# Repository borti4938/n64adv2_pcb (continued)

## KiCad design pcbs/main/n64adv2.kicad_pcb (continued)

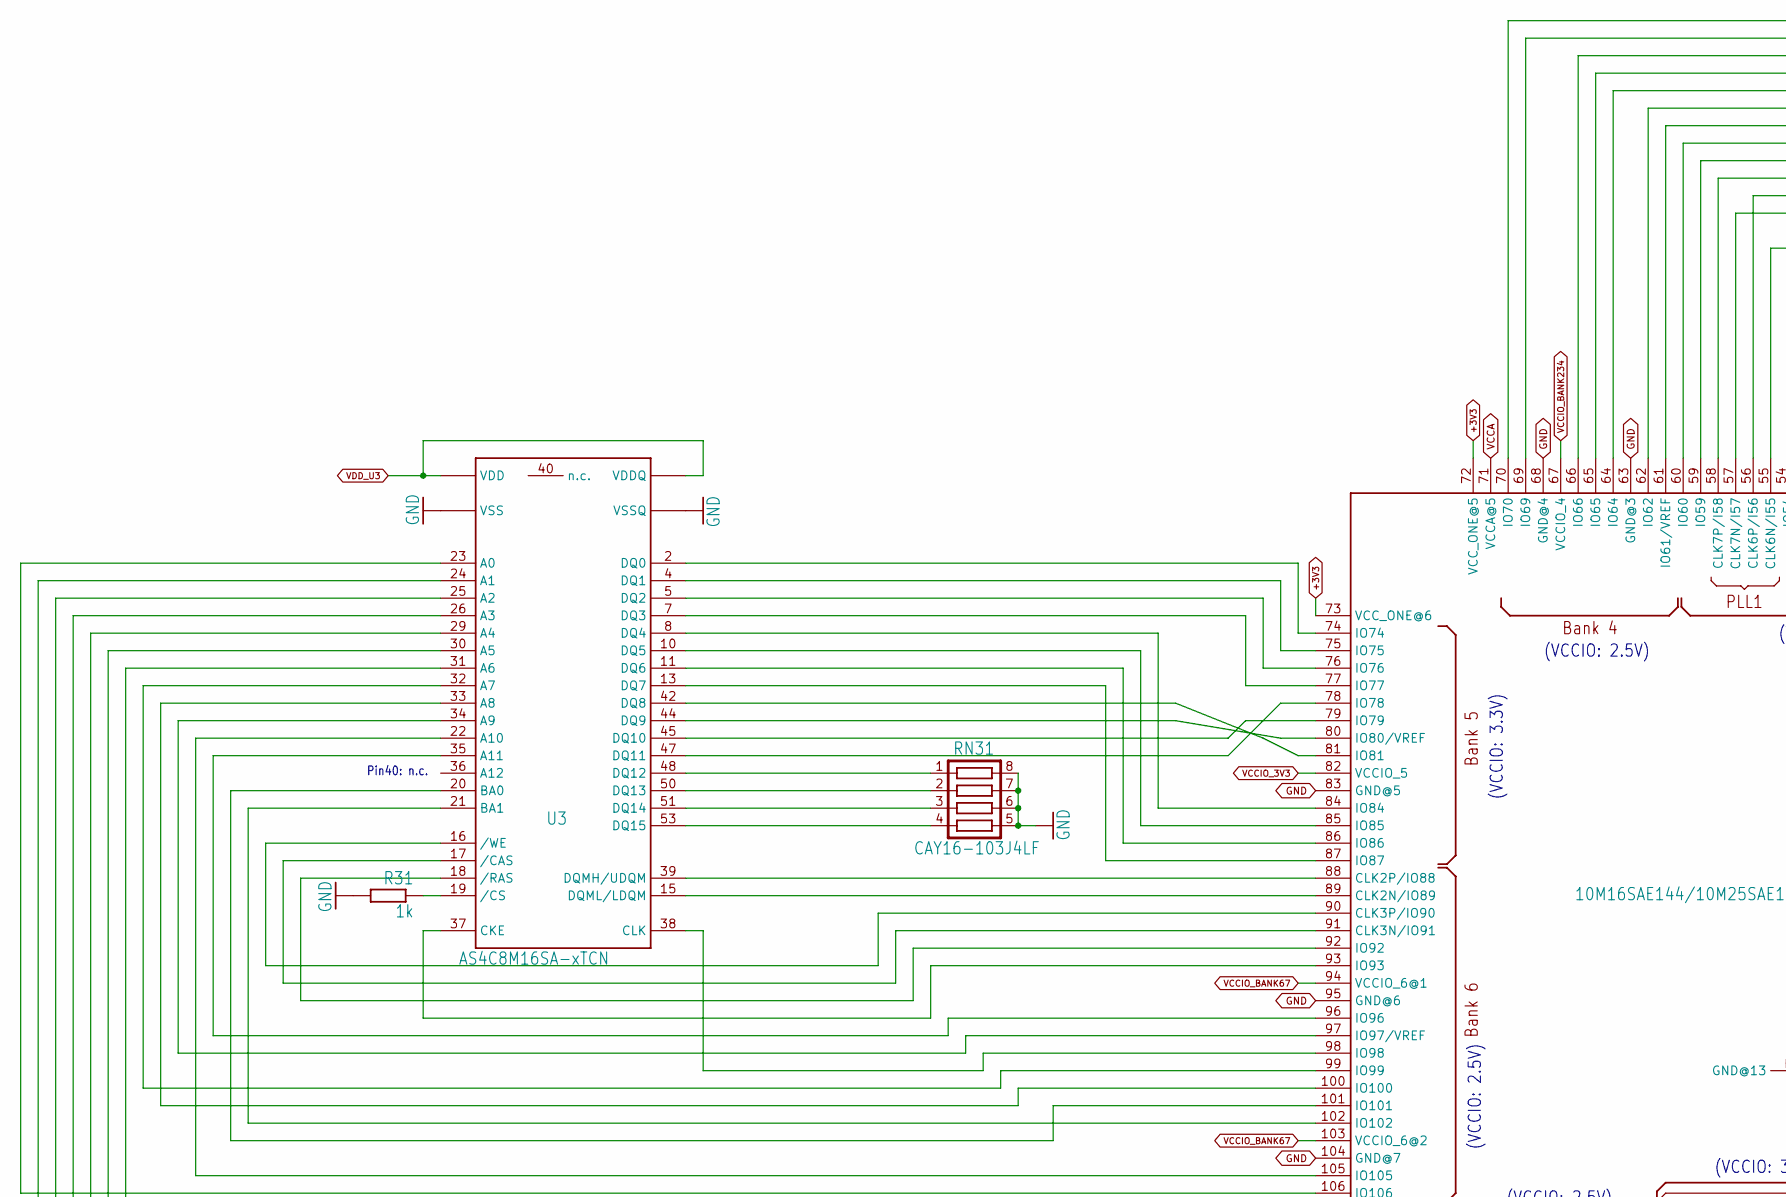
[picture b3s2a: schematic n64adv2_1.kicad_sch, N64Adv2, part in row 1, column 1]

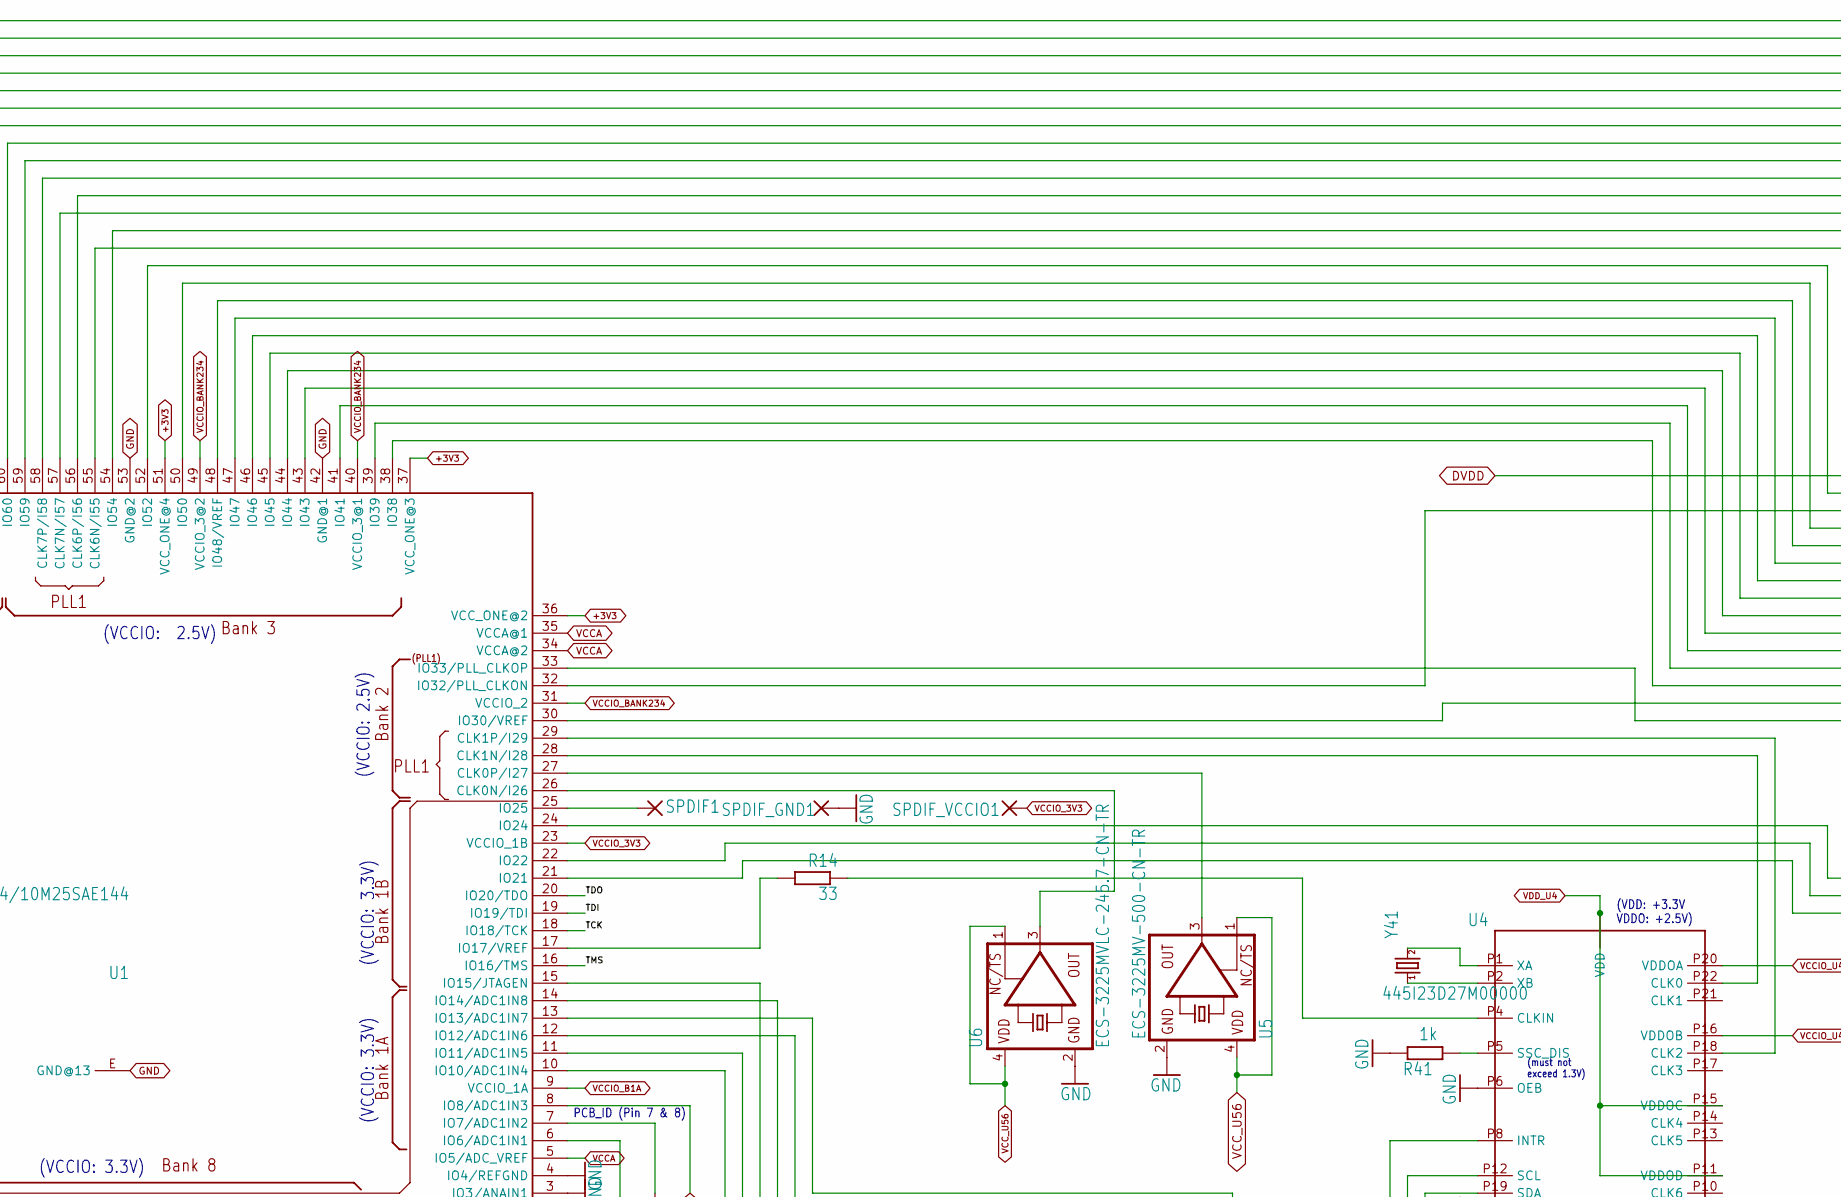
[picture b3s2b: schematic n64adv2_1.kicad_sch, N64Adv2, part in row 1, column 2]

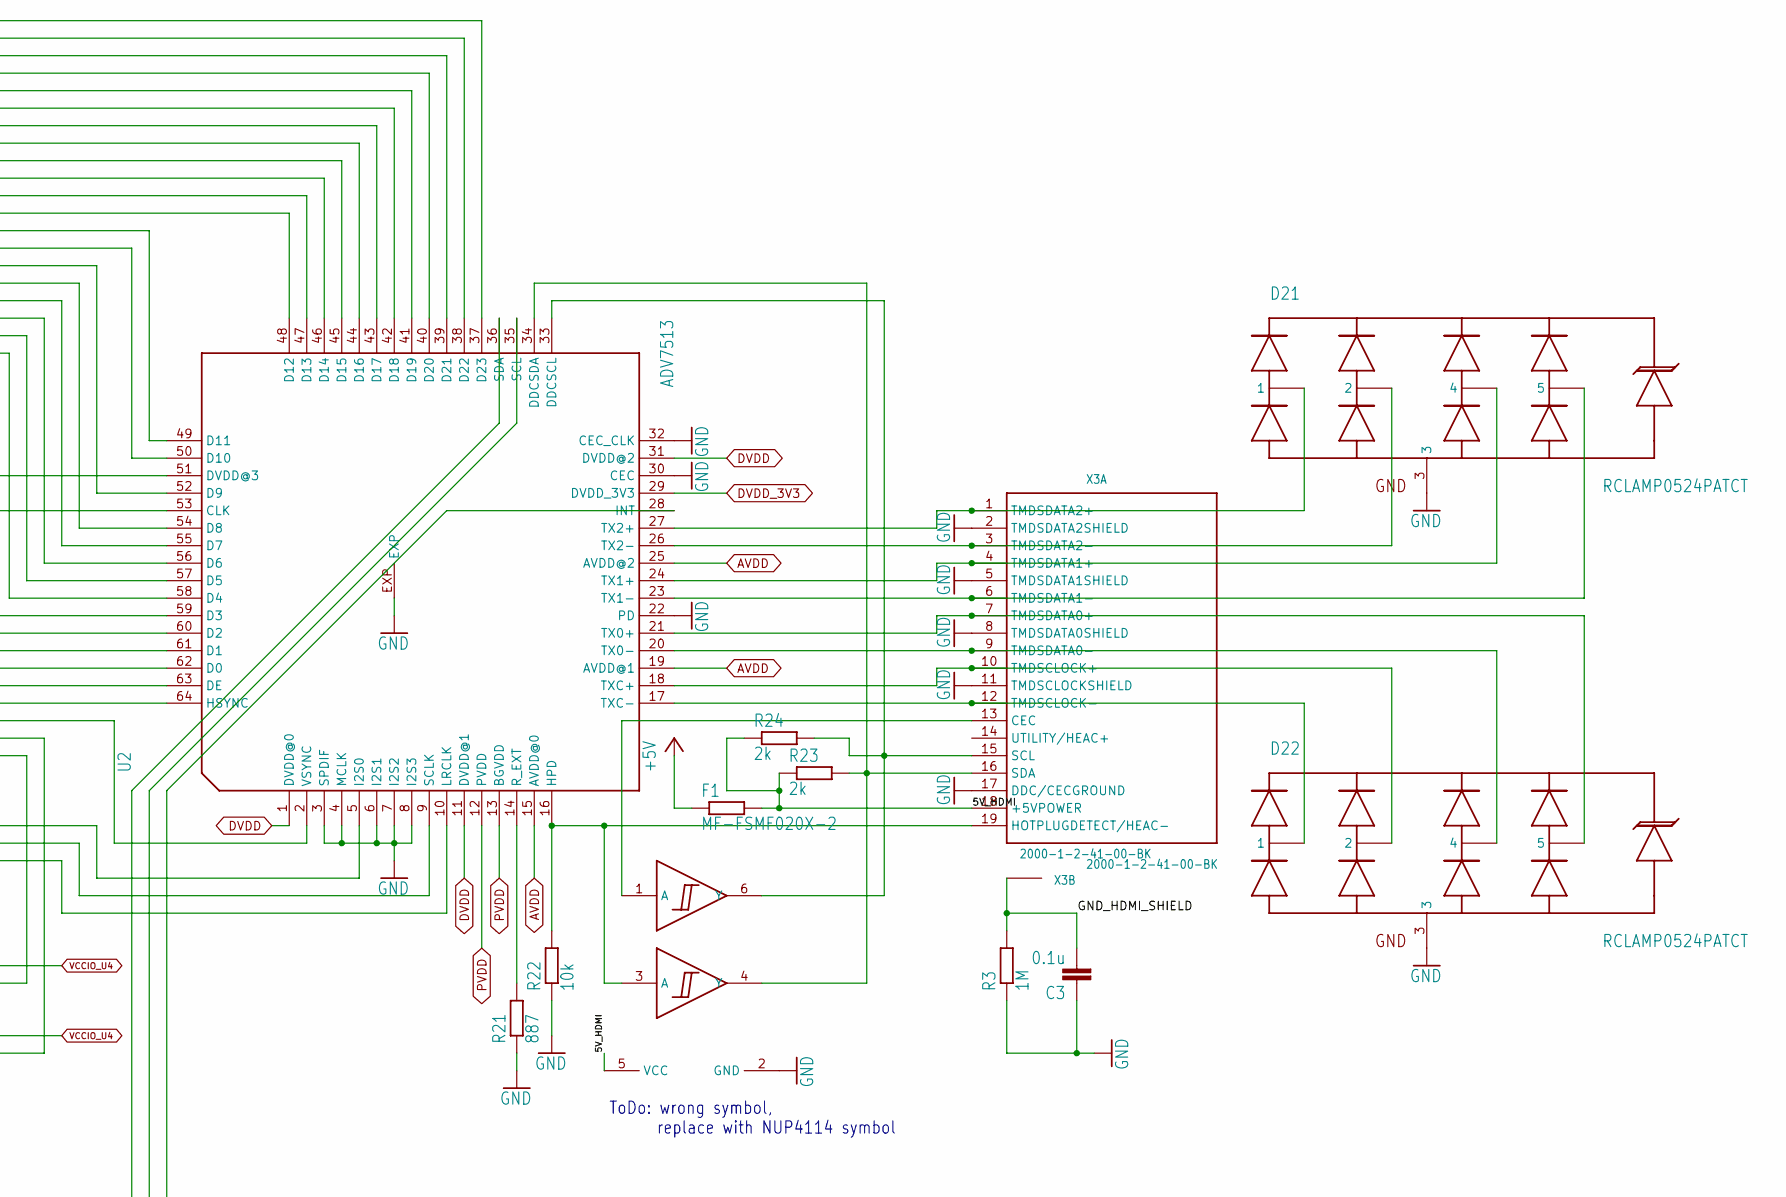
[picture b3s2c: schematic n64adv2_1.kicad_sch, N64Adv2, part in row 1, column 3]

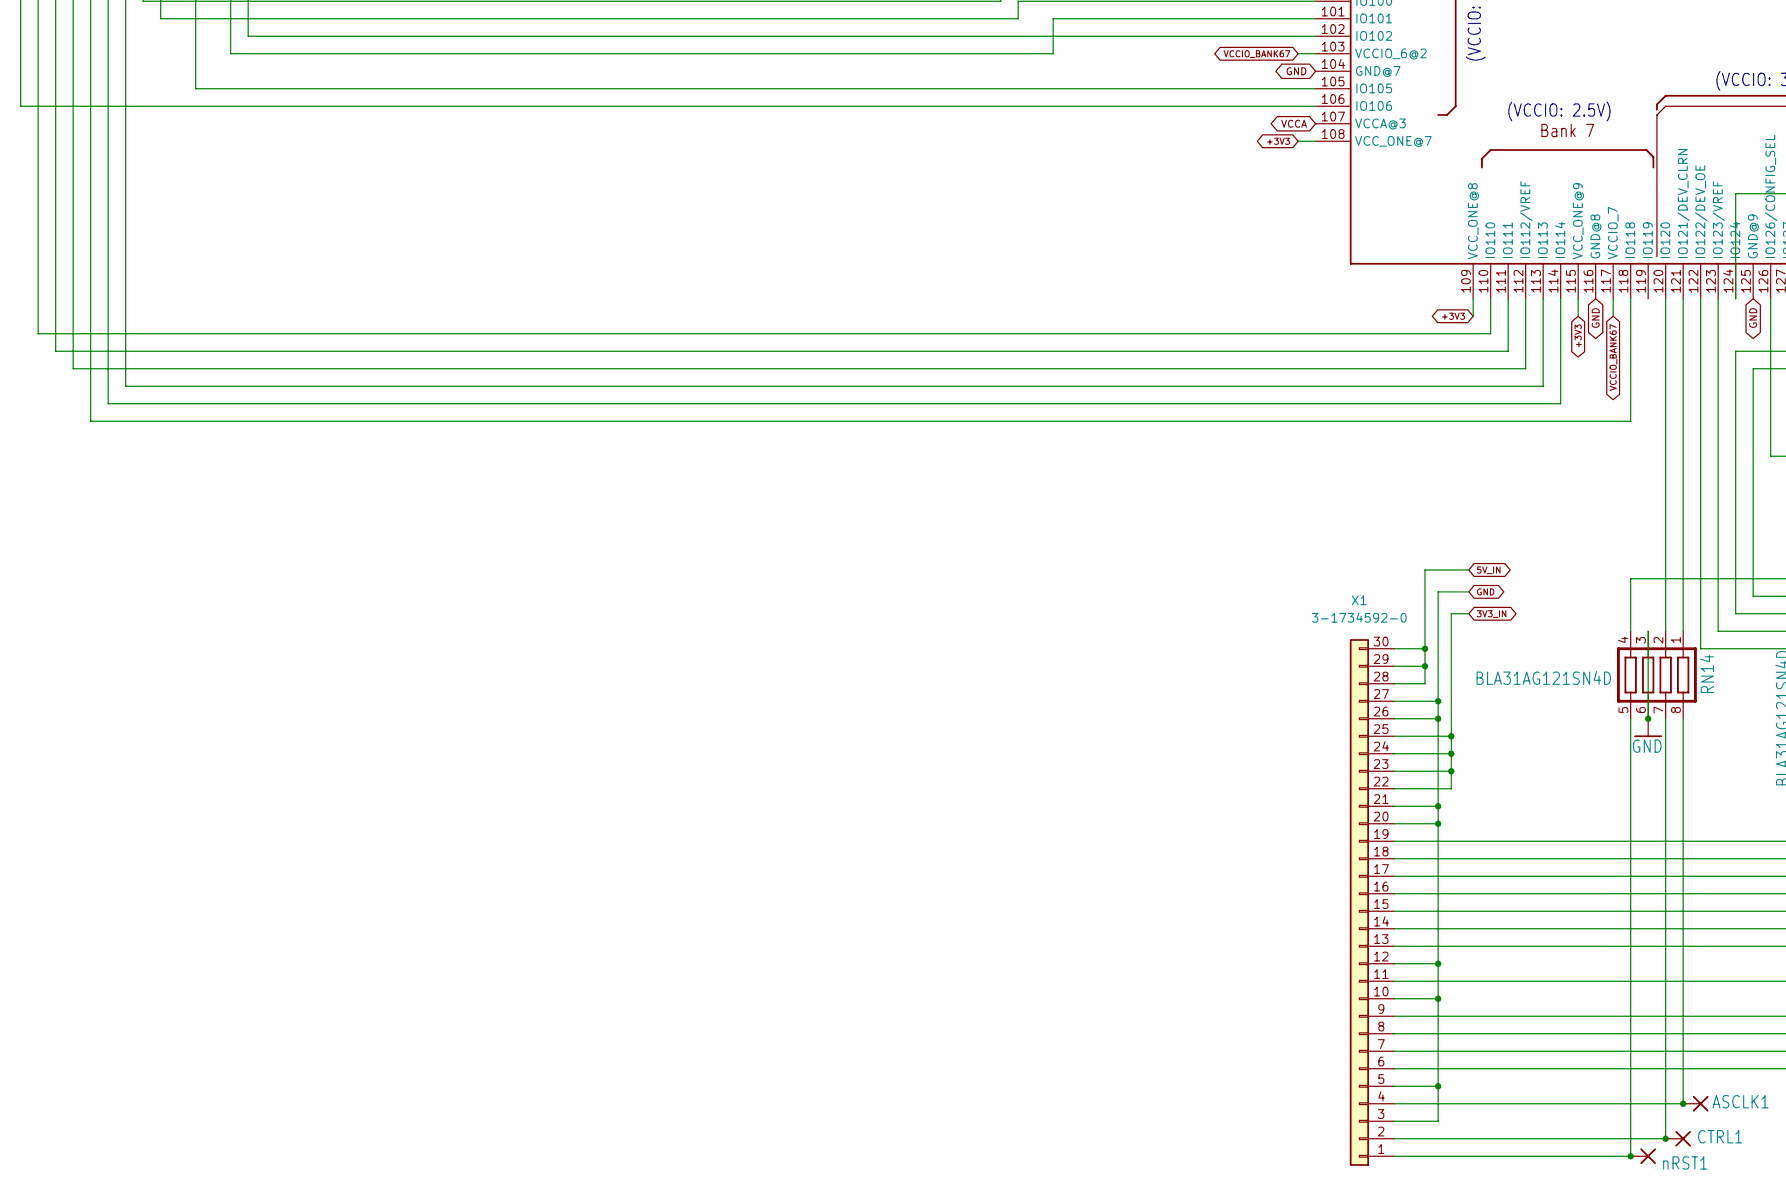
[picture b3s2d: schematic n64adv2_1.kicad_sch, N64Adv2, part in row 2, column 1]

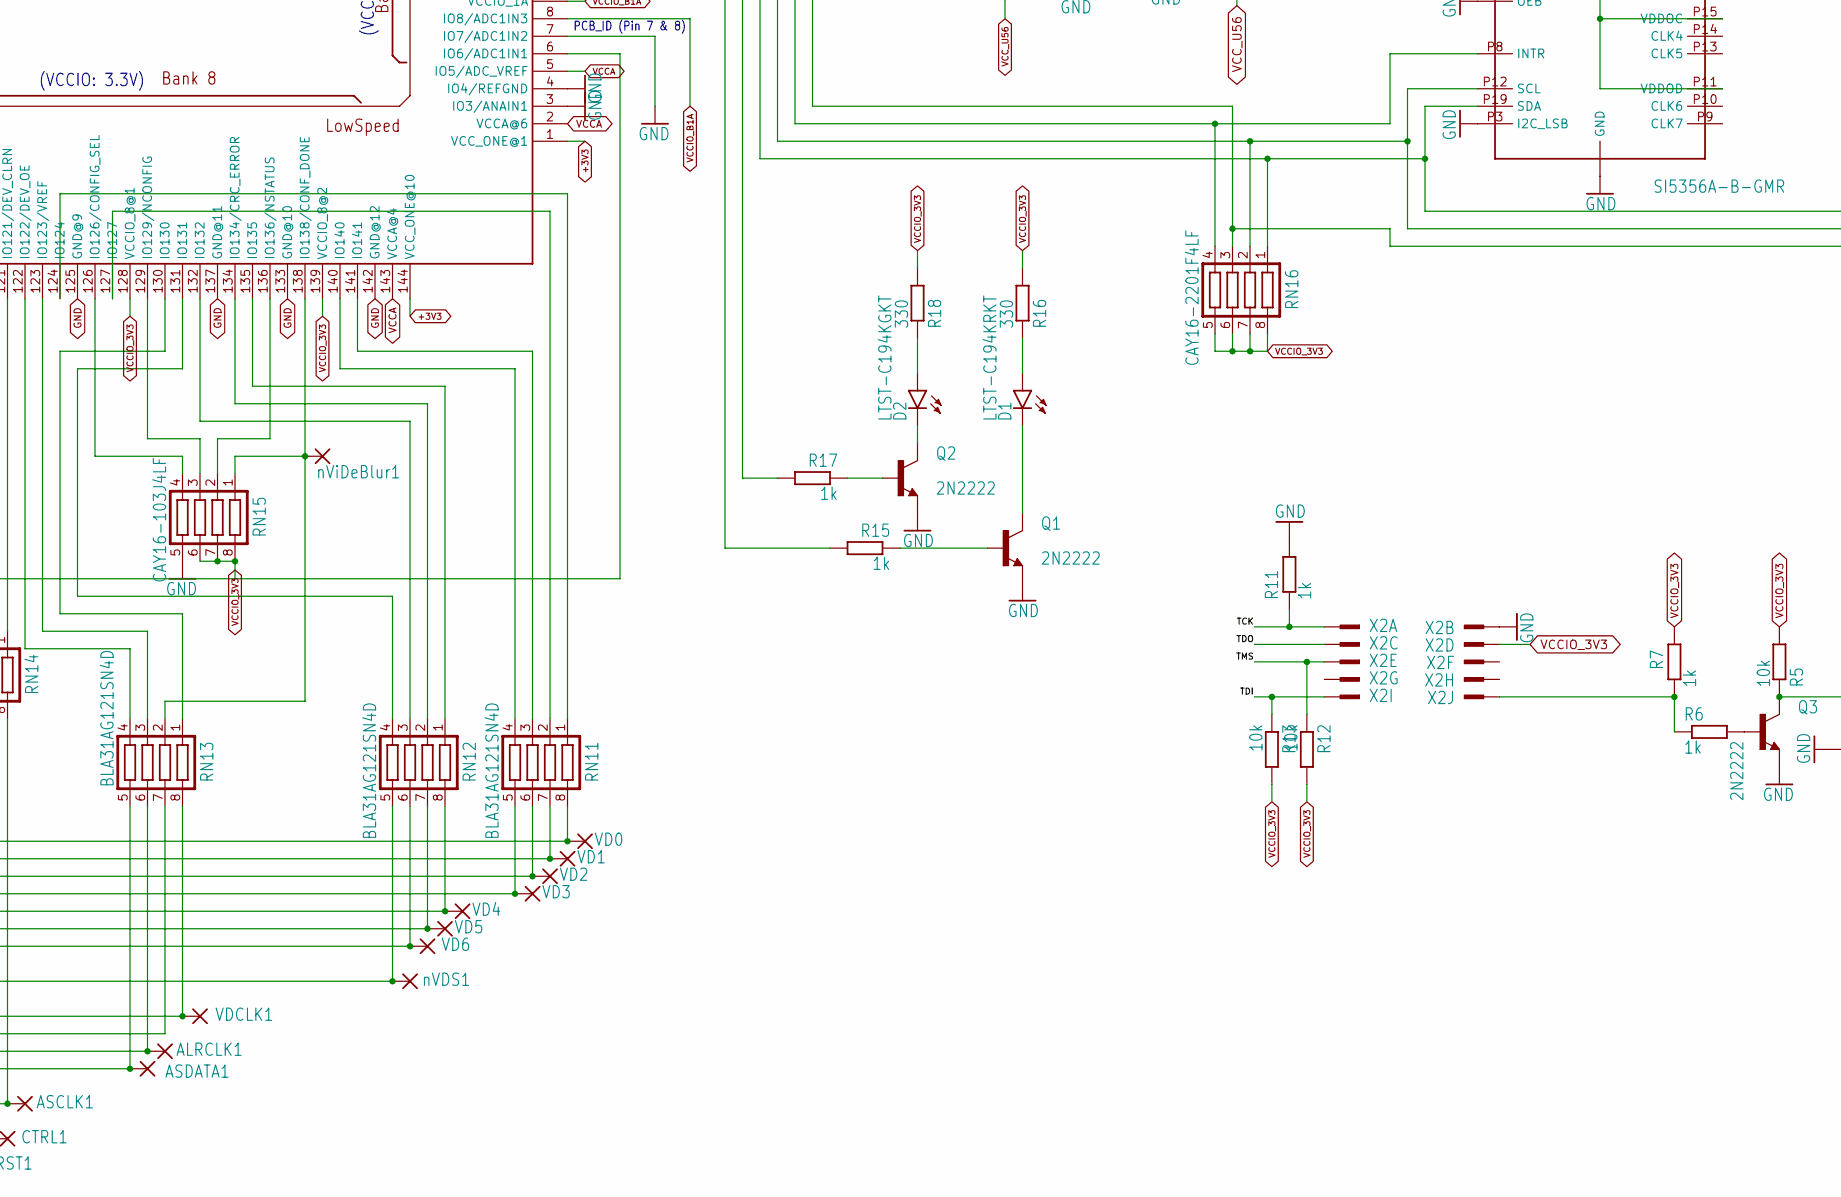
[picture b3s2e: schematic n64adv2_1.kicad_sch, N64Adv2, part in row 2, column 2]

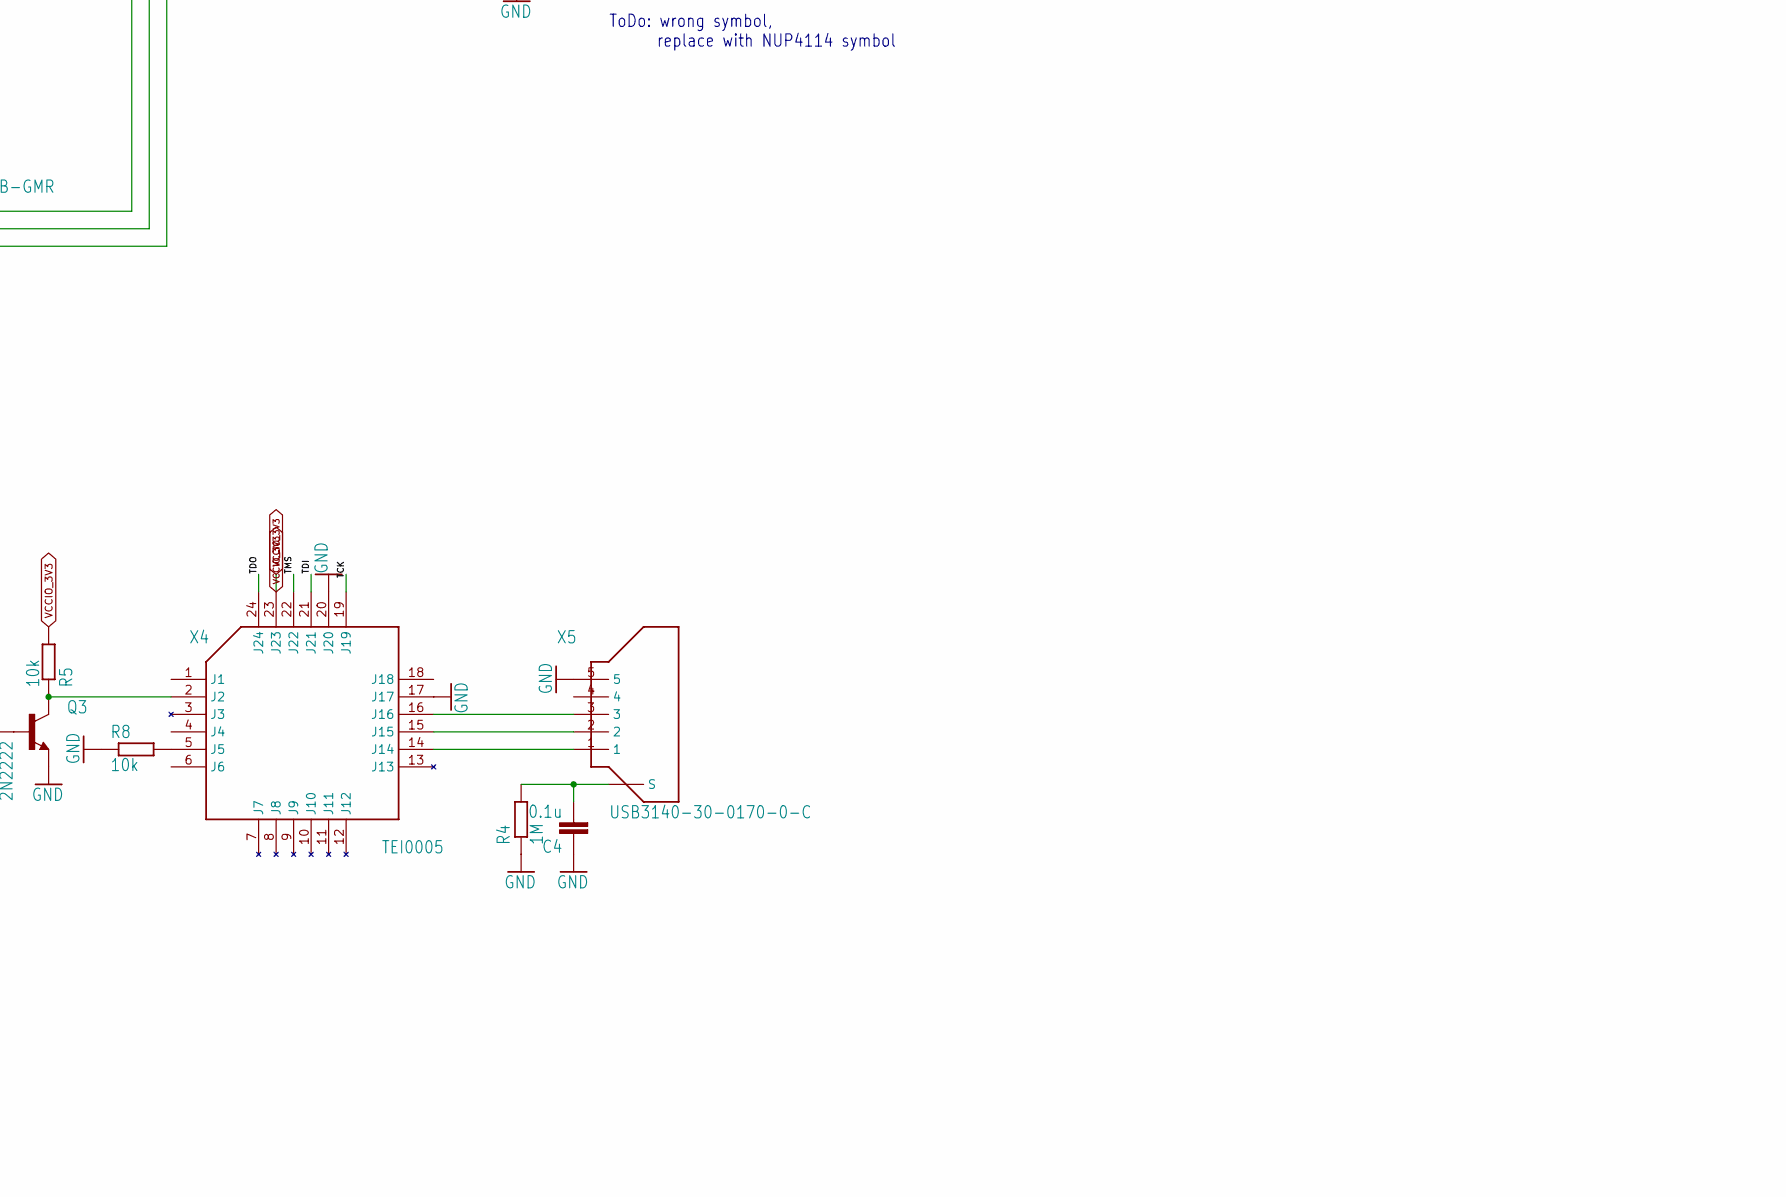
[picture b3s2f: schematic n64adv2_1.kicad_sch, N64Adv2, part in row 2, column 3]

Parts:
ALRCLK1: SMD1; SMD0,8-1,6
ASCLK1: SMD1; SMD0,8-1,6
ASDATA1: SMD1; SMD0,8-1,6
C3, C4: 0.1u; C0603
CTRL1: SMD1; SMD0,8-1,6
D1: LTST-C194KRKT; CHIPLED_0805
D2: LTST-C194KGKT; CHIPLED_0805
D21, D22: RCLAMP0524PATCT; HDMI_RCLAMP
D23: NUP4114HMR6T1G; SOT-23-6
F1: MF-FSMF020X-2; R0603
Q1, Q2, Q3: 2N2222; SOT23
R3, R4: 1M; R0603
R5, R8, R12, R13, R22: 10k; R0603
R6, R7, R11, R15, R17, R31, R41: 1k; R0603
R14: 33; R0603
R16, R18: 330; R0603
R21: 887; R0603
R23, R24: 2k; R0603
RN11, RN12, RN13, RN14: BLA31AG121SN4D; CTS742C083
RN15, RN31: CAY16-103J4LF; CTS742C083
RN16: CAY16-2201F4LF; CTS742C083
SPDIF1: SMD1; SMD0,8-1,6
SPDIF_GND1: SMD1; SMD0,8-1,6
SPDIF_VCCIO1: SMD1; SMD0,8-1,6
U1: 10M16SAE144/10M25SAE144; EQFP144_2
U2: ADV7513; LQFP64_EP
U3: AS4C8M16SA-xTCN; TSOP-54
U4: SI5356A-B-GMR; QFN-24-DIY
U5: ECS-3225MV-500-CN-TR; 3.2X2.5_KXO-V96
U6: ECS-3225MVLC-245.7-CN-TR; 3.2X2.5_KXO-V96
VD0, VD1, VD2, VD3, VD4, VD5, VD6: SMD1; SMD0,8-1,6
VDCLK1: SMD1; SMD0,8-1,6
X1: 3-1734592-0; FH12-30S-0.5SH
X2: 3020-10-0300-00; PAK100_2500-10
X3: 2000-1-2-41-00-BK; hdmi_smd_shield_2000-1-2-41-00-BK
X4: TEI0005
X5: USB3140-30-0170-0-C; USB-MICRO-VERTICAL-DIY
Y41: 445I23D27M00000; 5.0X3.2_2
nRST1: SMD1; SMD0,8-1,6
nVDS1: SMD1; SMD0,8-1,6
nViDeBlur1: SMD1; SMD0,8-1,6

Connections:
3V3_IN: X1.22, X1.23, X1.24, X1.25; also elsewhere on the board
5V_IN: X1.28, X1.29, X1.30; also elsewhere on the board
+3V3: U1.1 (VCC_ONE@1), U1.36 (VCC_ONE@2), U1.37 (VCC_ONE@3), U1.51 (VCC_ONE@4), U1.72 (VCC_ONE@5), U1.73 (VCC_ONE@6), U1.108 (VCC_ONE@7), U1.109 (VCC_ONE@8), U1.115 (VCC_ONE@9), U1.144 (VCC_ONE@10); also elsewhere on the board
+5V: F1.1; also elsewhere on the board
/n64adv2_logic/5V_HDMI: D23.5 (VCC), F1.2, R23.1, R24.1, X3.18 (+5VPOWER)
/n64adv2_logic/GND_HDMI_SHIELD: C3.2, R3.2, X3.SHELL (SHIELD), X3.SHELL1 (SHIELD), X3.SHELL2 (SHIELD), X3.SHELL3 (SHIELD)
/n64adv2_logic/TCK: R11.1, U1.18 (IO18/TCK), X2.1 (KL), X4.19 (J19)
/n64adv2_logic/TDI: R13.1, U1.19 (IO19/TDI), X2.9 (KL), X4.21 (J21)
/n64adv2_logic/TDO: U1.20 (IO20/TDO), X2.3 (KL), X4.24 (J24)
/n64adv2_logic/TMS: R12.1, U1.16 (IO16/TMS), X2.5 (KL), X4.22 (J22)
AVDD: U2.15 (AVDD@0), U2.19 (AVDD@1), U2.25 (AVDD@2); also elsewhere on the board
DVDD: U2.1 (DVDD@0), U2.11 (DVDD@1), U2.31 (DVDD@2), U2.51 (DVDD@3); also elsewhere on the board
DVDD_3V3: U2.29 (DVDD_3V3); also elsewhere on the board
GND: C3.1, C4.1, D21.3, D22.3, D23.2 (GND), Q1.2 (E), Q2.2 (E), Q3.2 (E), R3.1, R4.1, R8.1, R11.2, R21.1, R22.1, R31.2, R41.2, RN14.3, RN14.6, RN15.5, RN31.5, RN31.6, RN31.7, RN31.8, SPDIF_GND1.P$1, U1.3 (IO3/ANAIN1), U1.4 (IO4/REFGND), U1.7 (IO7/ADC1IN2), U1.42 (GND@1), U1.53 (GND@2), U1.63 (GND@3), U1.68 (GND@4), U1.83 (GND@5), U1.95 (GND@6), U1.104 (GND@7), U1.116 (GND@8), U1.125 (GND@9), U1.133 (GND@10), U1.137 (GND@11), U1.142 (GND@12), U1.E (GND@13), U2.3 (SPDIF), U2.4 (MCLK), U2.6 (I2S1), U2.7 (I2S2), U2.8 (I2S3), U2.22 (PD), U2.30 (CEC), U2.32 (CEC_CLK), U2.EXP, U3.6 (VSSQ), U3.12 (VSSQ), U3.28 (VSS), U3.41 (VSS), U3.46 (VSSQ), U3.52 (VSSQ), U3.54 (VSS), U4.EXP (GND), U4.P3 (I2C_LSB), U4.P6 (OEB), U4.P23 (GND), U5.2 (GND), U6.2 (GND), X1.3, X1.5, X1.10, X1.12, X1.20, X1.21, X1.26, X1.27, X2.2 (KL), X3.2 (TMDSDATA2SHIELD), X3.5 (TMDSDATA1SHIELD), X3.8 (TMDSDATA0SHIELD), X3.11 (TMDSCLOCKSHIELD), X3.17 (DDC/CECGROUND), X4.17 (J17), X4.20 (J20), X5.5; also elsewhere on the board
unnamed: ALRCLK1.P$1, RN13.6, X1.7
unnamed: ASCLK1.P$1, RN14.8, X1.4
unnamed: ASDATA1.P$1, RN13.5, X1.6
unnamed: C4.2, R4.2, X5.6 (S), X5.7 (S)
unnamed: CTRL1.P$1, RN14.7, X1.2
unnamed: D1.A, R16.1
unnamed: D1.C, Q1.3 (C)
unnamed: D2.A, R18.1
unnamed: D2.C, Q2.3 (C)
unnamed: D21.1, D21.10 (1), U2.27 (TX2+), X3.1 (TMDSDATA2+)
unnamed: D21.2, D21.9 (2), U2.26 (TX2-), X3.3 (TMDSDATA2-)
unnamed: D21.4, D21.7 (4), U2.24 (TX1+), X3.4 (TMDSDATA1+)
unnamed: D21.5, D21.6 (5), U2.23 (TX1-), X3.6 (TMDSDATA1-)
unnamed: D22.1, D22.10 (1), U2.17 (TXC-), X3.12 (TMDSCLOCK-)
unnamed: D22.2, D22.9 (2), U2.18 (TXC+), X3.10 (TMDSCLOCK+)
unnamed: D22.4, D22.7 (4), U2.20 (TX0-), X3.9 (TMDSDATA0-)
unnamed: D22.5, D22.6 (5), U2.21 (TX0+), X3.7 (TMDSDATA0+)
unnamed: D23.1 (A), X3.13 (CEC)
unnamed: D23.3 (A), R22.2, U2.16 (HPD), X3.19 (HOTPLUGDETECT/HEAC-)
unnamed: D23.4 (Y), R23.2, U2.34 (DDCSDA), X3.16 (SDA)
unnamed: D23.6 (Y), R24.2, U2.33 (DDCSCL), X3.15 (SCL)
unnamed: Q1.1 (B), R15.1
unnamed: Q2.1 (B), R17.1
unnamed: Q3.1 (B), R6.2
unnamed: Q3.3 (C), R5.1, X4.2 (J2)
unnamed: R6.1, R7.1, X2.10 (KL)
unnamed: R8.2, X4.5 (J5)
unnamed: R14.1, U4.P4 (CLKIN)
unnamed: R14.2, U1.17 (IO17/VREF)
unnamed: R15.2, U1.10 (IO10/ADC1IN4)
unnamed: R17.2, U1.11 (IO11/ADC1IN5)
unnamed: R21.2, U2.14 (R_EXT)
unnamed: R31.1, U3.19 (/CS)
unnamed: R41.1, U4.P5 (SSC_DIS)
unnamed: RN11.1, U1.124 (IO124)
unnamed: RN11.2, U1.127 (IO127)
unnamed: RN11.3, U1.141 (IO141)
unnamed: RN11.4, U1.140 (IO140)
unnamed: RN11.5, VD3.P$1, X1.16
unnamed: RN11.6, VD2.P$1, X1.17
unnamed: RN11.7, VD1.P$1, X1.18
unnamed: RN11.8, VD0.P$1, X1.19
unnamed: RN12.1, U1.135 (IO135)
unnamed: RN12.2, U1.134 (IO134/CRC_ERROR)
unnamed: RN12.3, U1.132 (IO132)
unnamed: RN12.4, U1.131 (IO131)
unnamed: RN12.5, X1.11, nVDS1.P$1
unnamed: RN12.6, VD6.P$1, X1.13
unnamed: RN12.7, VD5.P$1, X1.14
unnamed: RN12.8, VD4.P$1, X1.15
unnamed: RN13.1, U1.130 (IO130)
unnamed: RN13.2, RN15.1, U1.138 (IO138/CONF_DONE), nViDeBlur1.P$1
unnamed: RN13.3, U1.123 (IO123/VREF)
unnamed: RN13.4, U1.122 (IO122/DEV_OE)
unnamed: RN13.7, X1.8
unnamed: RN13.8, VDCLK1.P$1, X1.9
unnamed: RN14.1, U1.121 (IO121/DEV_CLRN)
unnamed: RN14.2, U1.120 (IO120)
unnamed: RN14.4, U1.6 (IO6/ADC1IN1)
unnamed: RN14.5, X1.1, nRST1.P$1
unnamed: RN15.2, U1.136 (IO136/NSTATUS)
unnamed: RN15.3, U1.129 (IO129/NCONFIG)
unnamed: RN15.4, U1.126 (IO126/CONFIG_SEL)
unnamed: RN16.1, U1.15 (IO15/JTAGEN), U2.36 (SDA), U4.P19 (SDA)
unnamed: RN16.2, U1.14 (IO14/ADC1IN8), U2.35 (SCL), U4.P12 (SCL)
unnamed: RN16.3, U1.13 (IO13/ADC1IN7), U2.28 (INT)
unnamed: RN16.4, U1.12 (IO12/ADC1IN6), U4.P8 (INTR)
unnamed: RN31.1, U3.48 (DQ12)
unnamed: RN31.2, U3.50 (DQ13)
unnamed: RN31.3, U3.51 (DQ14)
unnamed: RN31.4, U3.53 (DQ15)
unnamed: SPDIF1.P$1, U1.25 (IO25)
unnamed: U1.21 (IO21), U2.10 (LRCLK)
unnamed: U1.22 (IO22), U2.9 (SCLK)
unnamed: U1.24 (IO24), U2.5 (I2S0)
unnamed: U1.26 (CLK0N/I26), U6.3 (OUT)
unnamed: U1.27 (CLK0P/I27), U5.3 (OUT)
unnamed: U1.28 (CLK1N/I28), U4.P22 (CLK0)
unnamed: U1.29 (CLK1P/I29), U4.P18 (CLK2)
unnamed: U1.30 (IO30/VREF), U2.64 (HSYNC)
unnamed: U1.32 (IO32/PLL_CLKON), U2.53 (CLK)
unnamed: U1.33 (IO33/PLL_CLKOP), U2.2 (VSYNC)
unnamed: U1.38 (IO38), U2.63 (DE)
unnamed: U1.39 (IO39), U2.62 (D0)
unnamed: U1.41 (IO41), U2.61 (D1)
unnamed: U1.43 (IO43), U2.60 (D2)
unnamed: U1.44 (IO44), U2.59 (D3)
unnamed: U1.45 (IO45), U2.58 (D4)
unnamed: U1.46 (IO46), U2.57 (D5)
unnamed: U1.47 (IO47), U2.56 (D6)
unnamed: U1.48 (IO48/VREF), U2.55 (D7)
unnamed: U1.50 (IO50), U2.54 (D8)
unnamed: U1.52 (IO52), U2.52 (D9)
unnamed: U1.54 (IO54), U2.49 (D11)
unnamed: U1.55 (CLK6N/I55), U2.50 (D10)
unnamed: U1.56 (CLK6P/I56), U2.47 (D13)
unnamed: U1.57 (CLK7N/I57), U2.48 (D12)
unnamed: U1.58 (CLK7P/I58), U2.46 (D14)
unnamed: U1.59 (IO59), U2.45 (D15)
unnamed: U1.60 (IO60), U2.44 (D16)
unnamed: U1.61 (IO61/VREF), U2.43 (D17)
unnamed: U1.62 (IO62), U2.42 (D18)
unnamed: U1.64 (IO64), U2.41 (D19)
unnamed: U1.65 (IO65), U2.40 (D20)
unnamed: U1.66 (IO66), U2.39 (D21)
unnamed: U1.69 (IO69), U2.38 (D22)
unnamed: U1.70 (IO70), U2.37 (D23)
unnamed: U1.74 (IO74), U3.2 (DQ0)
unnamed: U1.75 (IO75), U3.4 (DQ1)
unnamed: U1.76 (IO76), U3.5 (DQ2)
unnamed: U1.77 (IO77), U3.7 (DQ3)
unnamed: U1.78 (IO78), U3.47 (DQ11)
unnamed: U1.79 (IO79), U3.45 (DQ10)
unnamed: U1.80 (IO80/VREF), U3.44 (DQ9)
unnamed: U1.81 (IO81), U3.42 (DQ8)
unnamed: U1.84 (IO84), U3.8 (DQ4)
unnamed: U1.85 (IO85), U3.10 (DQ5)
unnamed: U1.86 (IO86), U3.11 (DQ6)
unnamed: U1.87 (IO87), U3.13 (DQ7)
unnamed: U1.88 (CLK2P/IO88), U3.39 (DQMH/UDQM)
unnamed: U1.89 (CLK2N/IO89), U3.15 (DQML/LDQM)
unnamed: U1.90 (CLK3P/IO90), U3.16 (/WE)
unnamed: U1.91 (CLK3N/IO91), U3.17 (/CAS)
unnamed: U1.92 (IO92), U3.18 (/RAS)
unnamed: U1.93 (IO93), U3.37 (CKE)
unnamed: U1.96 (IO96), U3.35 (A11)
unnamed: U1.97 (IO97/VREF), U3.34 (A9)
unnamed: U1.98 (IO98), U3.38 (CLK)
unnamed: U1.99 (IO99), U3.32 (A7)
unnamed: U1.100 (IO100), U3.33 (A8)
unnamed: U1.101 (IO101), U3.20 (BA0)
unnamed: U1.102 (IO102), U3.21 (BA1)
unnamed: U1.105 (IO105), U3.22 (A10)
unnamed: U1.106 (IO106), U3.23 (A0)
unnamed: U1.110 (IO110), U3.24 (A1)
unnamed: U1.111 (IO111), U3.25 (A2)
unnamed: U1.112 (IO112/VREF), U3.26 (A3)
unnamed: U1.113 (IO113), U3.31 (A6)
unnamed: U1.114 (IO114), U3.30 (A5)
unnamed: U1.118 (IO118), U3.29 (A4)
unnamed: U4.P1 (XA), Y41.2
unnamed: U4.P2 (XB), Y41.1
unnamed: X4.14 (J14), X5.1
unnamed: X4.15 (J15), X5.2
unnamed: X4.16 (J16), X5.3
PVDD: U2.12 (PVDD), U2.13 (BGVDD); also elsewhere on the board
VCCA: U1.2 (VCCA@6), U1.5 (IO5/ADC_VREF), U1.34 (VCCA@2), U1.35 (VCCA@1), U1.71 (VCCA@5), U1.107 (VCCA@3), U1.143 (VCCA@4); also elsewhere on the board
VCCIO_2V5: U1.31 (VCCIO_2), U1.40 (VCCIO_3@1), U1.49 (VCCIO_3@2), U1.67 (VCCIO_4); also elsewhere on the board
VCCIO_3V3: R5.2, R7.2, R12.2, R13.2, R16.2, R18.2, RN15.6, RN15.7, RN15.8, RN16.5, RN16.6, RN16.7, RN16.8, SPDIF_VCCIO1.P$1, U1.23 (VCCIO_1B), U1.82 (VCCIO_5), U1.128 (VCCIO_8@1), U1.139 (VCCIO_8@2), X2.4 (KL), X4.23 (J23); also elsewhere on the board
VCCIO_B1A: U1.8 (IO8/ADC1IN3), U1.9 (VCCIO_1A); also elsewhere on the board
VCCIO_BANK67: U1.94 (VCCIO_6@1), U1.103 (VCCIO_6@2), U1.117 (VCCIO_7); also elsewhere on the board
VCCIO_U4: U4.P16 (VDDOB), U4.P20 (VDDOA); also elsewhere on the board
VCC_U56: U5.1 (TS), U5.4 (VDD), U6.1 (TS), U6.4 (VDD); also elsewhere on the board
VDD_U3: U3.1 (VDD), U3.3 (VDDQ), U3.9 (VDDQ), U3.14 (VDD), U3.27 (VDD), U3.43 (VDDQ), U3.49 (VDDQ); also elsewhere on the board
VDD_U4: U4.P7 (VDD), U4.P11 (VDDOD), U4.P15 (VDDOC), U4.P24 (VDD); also elsewhere on the board

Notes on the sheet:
(VCCIO: 3.3V)
PCB_ID (Pin 7 & 8)
(VCCIO: 2.5V)
ToDo: wrong symbol, replace with NUP4114 symbol
(VDD: +3.3V VDDO: +2.5V)
Pin40: n.c.
(VCCIO: 2.5V)
(must not exceed 1.3V)

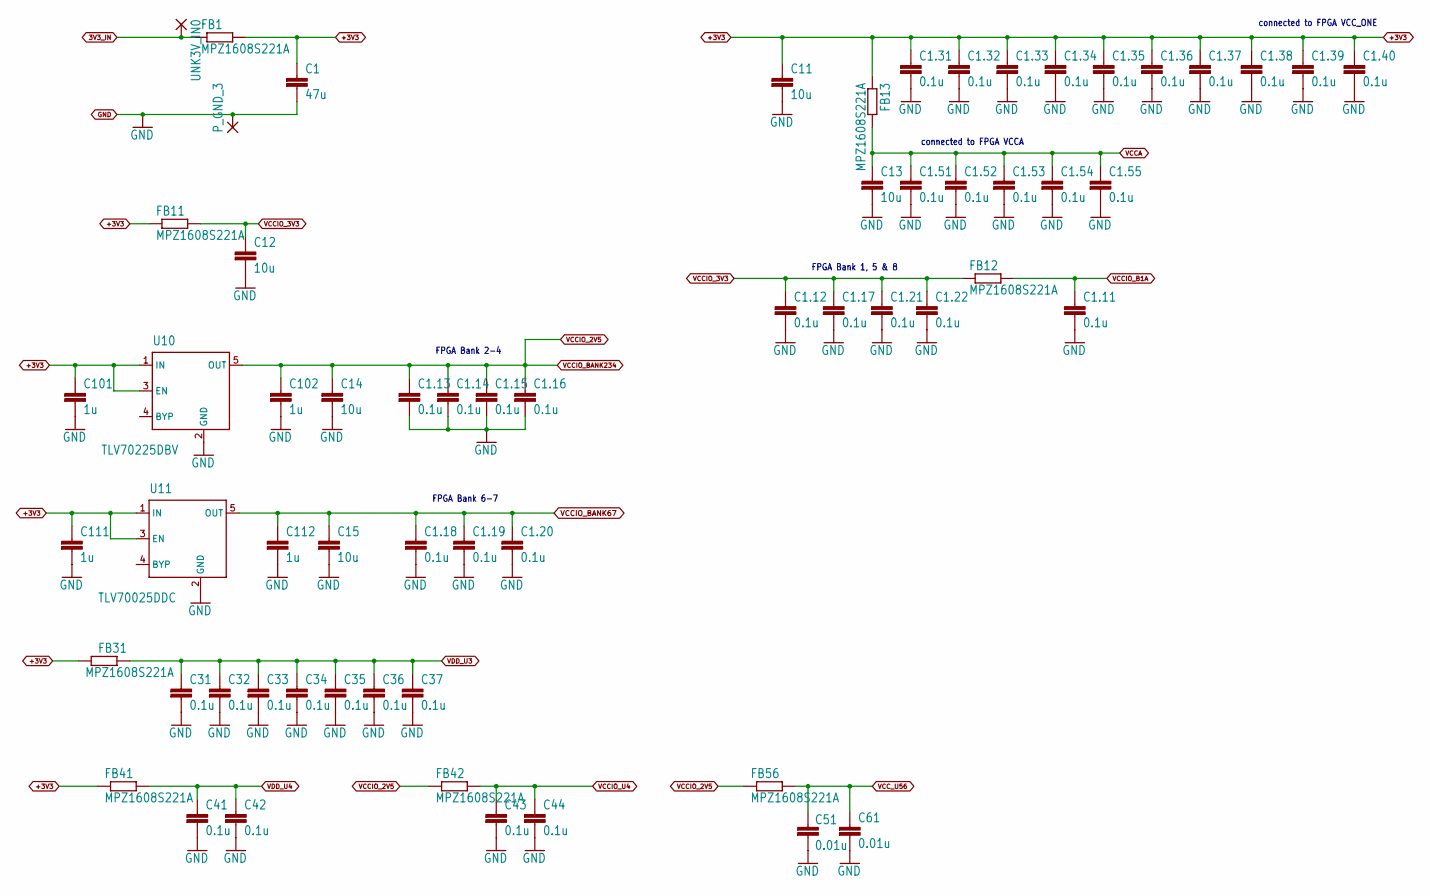
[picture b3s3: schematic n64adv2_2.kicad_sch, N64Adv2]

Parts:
C1: 47u; C0805
C1.11, C1.12, C1.13, C1.14, C1.15, C1.16, C1.17, C1.18, C1.19, C1.20, C1.21, C1.22, C1.31, C1.32, C1.33, C1.34, C1.35, C1.36, C1.37, C1.38, C1.39, C1.40, C1.51, C1.52, C1.53, C1.54, C1.55, C31, C32, C33, C34, C35, C36, C37, C41, C42, C43, C44: 0.1u; C0603
C11, C12, C13, C14, C15: 10u; C0805
C51, C61: 0.01u; C0603
C101, C102, C111, C112: 1u; C0603
FB1, FB11, FB12, FB13, FB31, FB41, FB42, FB56: MPZ1608S221A; R0603
P_GND_3: SMD2; SMD1,27-2,54
U10: TLV70225DBV; SOT23-5
U11: TLV70025DDC; SOT23-5
UNK3V_IN0: SMD2; SMD1,27-2,54

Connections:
3V3_IN: FB1.1, UNK3V_IN0.1; also elsewhere on the board
+3V3: C1.1, C1.31.1, C1.32.1, C1.33.1, C1.34.1, C1.35.1, C1.36.1, C1.37.1, C1.38.1, C1.39.1, C1.40.1, C11.1, C101.1, C111.1, FB1.2, FB11.1, FB13.1, FB31.1, FB41.1, U10.1 (IN), U10.3 (EN), U11.1 (IN), U11.3 (EN); also elsewhere on the board
GND: C1.2, C1.11.2, C1.12.2, C1.13.2, C1.14.2, C1.15.2, C1.16.2, C1.17.2, C1.18.2, C1.19.2, C1.20.2, C1.21.2, C1.22.2, C1.31.2, C1.32.2, C1.33.2, C1.34.2, C1.35.2, C1.36.2, C1.37.2, C1.38.2, C1.39.2, C1.40.2, C1.51.2, C1.52.2, C1.53.2, C1.54.2, C1.55.2, C11.2, C12.2, C13.2, C14.2, C15.2, C31.2, C32.2, C33.2, C34.2, C35.2, C36.2, C37.2, C41.2, C42.2, C43.2, C44.2, C51.2, C61.2, C101.2, C102.2, C111.2, C112.2, P_GND_3.1, U10.2 (GND), U11.2 (GND); also elsewhere on the board
VCCA: C1.51.1, C1.52.1, C1.53.1, C1.54.1, C1.55.1, C13.1, FB13.2; also elsewhere on the board
VCCIO_2V5: C1.13.1, C1.14.1, C1.15.1, C1.16.1, C14.1, C102.1, FB42.1, FB56.1, U10.5 (OUT); also elsewhere on the board
VCCIO_3V3: C1.12.1, C1.17.1, C1.21.1, C1.22.1, C12.1, FB11.2, FB12.1; also elsewhere on the board
VCCIO_B1A: C1.11.1, FB12.2; also elsewhere on the board
VCCIO_BANK67: C1.18.1, C1.19.1, C1.20.1, C15.1, C112.1, U11.5 (OUT); also elsewhere on the board
VCCIO_U4: C43.1, C44.1, FB42.2; also elsewhere on the board
VCC_U56: C51.1, C61.1, FB56.2; also elsewhere on the board
VDD_U3: C31.1, C32.1, C33.1, C34.1, C35.1, C36.1, C37.1, FB31.2; also elsewhere on the board
VDD_U4: C41.1, C42.1, FB41.2; also elsewhere on the board

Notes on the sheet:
connected to FPGA VCCA
connected to FPGA VCC_ONE
FPGA Bank 6-7
FPGA Bank 2-4
FPGA Bank 1, 5 & 8
